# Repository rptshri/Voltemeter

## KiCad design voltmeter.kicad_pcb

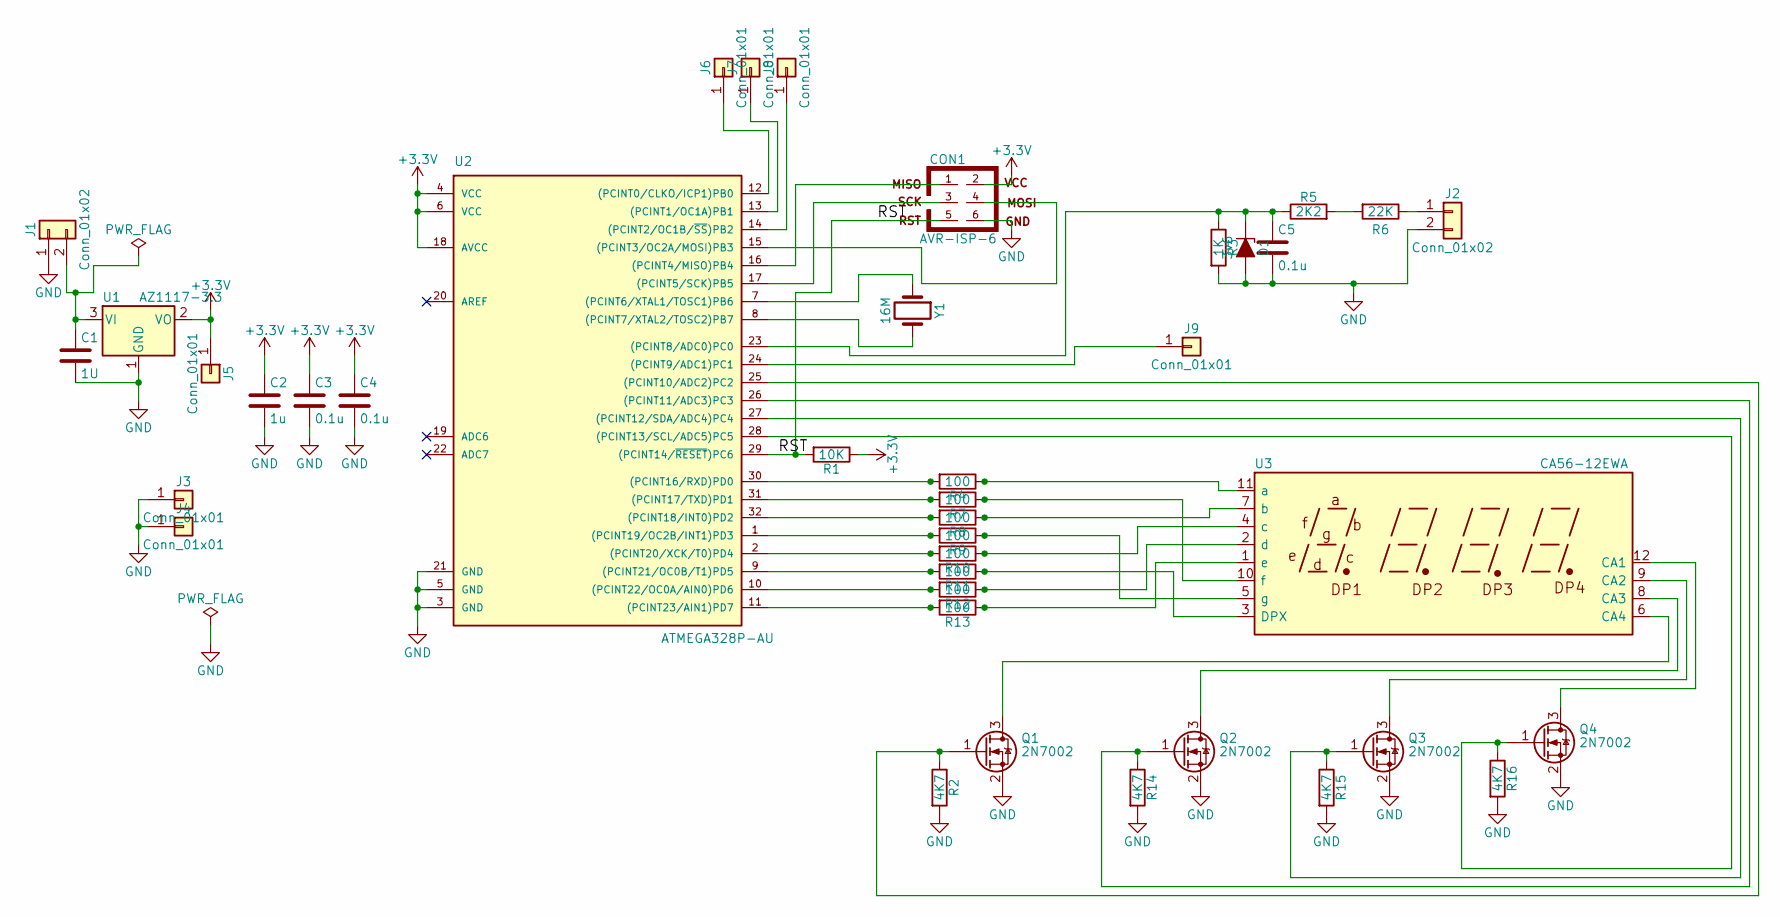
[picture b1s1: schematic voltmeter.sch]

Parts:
C1: 1U; C_0805_HandSoldering
C2: 1u; C_0805_HandSoldering
C3, C4, C5: 0.1u; C_0805_HandSoldering
CON1: AVR-ISP-6; Pin_Header_Straight_2x03_Pitch2.54mm
D1: 3v6; D_SMA
J1, J2: Conn_01x02; WAGO_734_2pin_Straight_RuggedPads
J3, J4, J5, J6, J7, J8, J9: Conn_01x01; Pin_Header_Straight_1x01_Pitch2.54mm
Q1, Q2, Q3, Q4: 2N7002; SOT-23
R1: 10K; R_0805_HandSoldering
R2, R14, R15, R16: 4K7; R_0805_HandSoldering
R3: 1K; R_0805_HandSoldering
R4, R7, R8, R9, R10, R11, R12, R13: 100; R_0805_HandSoldering
R5: 2K2; R_0805_HandSoldering
R6: 22K; R_0805_HandSoldering
U1: AZ1117-3.3; SOT-223-3_TabPin2
U2: ATMEGA328P-AU; TQFP-32_7x7mm_Pitch0.8mm
U3: CA56-12EWA
Y1: 16M; Crystal_HC18-U_Vertical

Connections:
+3V3: C2.1, C3.1, C4.1, CON1.2, J5.1, R1.1, U1.2 (VO), U2.4 (VCC), U2.6 (VCC), U2.18 (AVCC)
/RST: CON1.5, R1.2, U2.29 ((PCINT14/~RESET~)PC6)
GND: C1.2, C2.2, C3.2, C4.2, C5.2, CON1.6, D1.2 (A), J1.1, J2.2, J3.1, J4.1, Q1.2 (S), Q2.2 (S), Q3.2 (S), Q4.2 (S), R2.2, R3.2, R14.2, R15.2, R16.2, U1.1 (GND), U2.3 (GND), U2.5 (GND), U2.21 (GND)
unnamed: C1.1, J1.2, U1.3 (VI)
unnamed: C5.1, D1.1 (K), R3.1, R5.1, U2.23 ((PCINT8/ADC0)PC0)
unnamed: CON1.1, U2.16 ((PCINT4/MISO)PB4)
unnamed: CON1.3, U2.17 ((PCINT5/SCK)PB5)
unnamed: CON1.4, U2.15 ((PCINT3/OC2A/MOSI)PB3)
unnamed: J2.1, R6.1
unnamed: J6.1, U2.12 ((PCINT0/CLKO/ICP1)PB0)
unnamed: J7.1, U2.13 ((PCINT1/OC1A)PB1)
unnamed: J8.1, U2.14 ((PCINT2/OC1B/~SS~)PB2)
unnamed: J9.1, U2.24 ((PCINT9/ADC1)PC1)
unnamed: Q1.1 (G), R2.1, U2.25 ((PCINT10/ADC2)PC2)
unnamed: Q1.3 (D), U3.6 (CA4)
unnamed: Q2.1 (G), R14.1, U2.26 ((PCINT11/ADC3)PC3)
unnamed: Q2.3 (D), U3.8 (CA3)
unnamed: Q3.1 (G), R15.1, U2.27 ((PCINT12/SDA/ADC4)PC4)
unnamed: Q3.3 (D), U3.9 (CA2)
unnamed: Q4.1 (G), R16.1, U2.28 ((PCINT13/SCL/ADC5)PC5)
unnamed: Q4.3 (D), U3.12 (CA1)
unnamed: R4.1, U3.11 (a)
unnamed: R4.2, U2.30 ((PCINT16/RXD)PD0)
unnamed: R5.2, R6.2
unnamed: R7.1, U3.10 (f)
unnamed: R7.2, U2.31 ((PCINT17/TXD)PD1)
unnamed: R8.1, U3.7 (b)
unnamed: R8.2, U2.32 ((PCINT18/INT0)PD2)
unnamed: R9.1, U3.5 (g)
unnamed: R9.2, U2.1 ((PCINT19/OC2B/INT1)PD3)
unnamed: R10.1, U3.4 (c)
unnamed: R10.2, U2.2 ((PCINT20/XCK/T0)PD4)
unnamed: R11.1, U3.3 (DPX)
unnamed: R11.2, U2.9 ((PCINT21/OC0B/T1)PD5)
unnamed: R12.1, U3.2 (d)
unnamed: R12.2, U2.10 ((PCINT22/OC0A/AIN0)PD6)
unnamed: R13.1, U3.1 (e)
unnamed: R13.2, U2.11 ((PCINT23/AIN1)PD7)
unnamed: U2.7 ((PCINT6/XTAL1/TOSC1)PB6), Y1.1
unnamed: U2.8 ((PCINT7/XTAL2/TOSC2)PB7), Y1.2

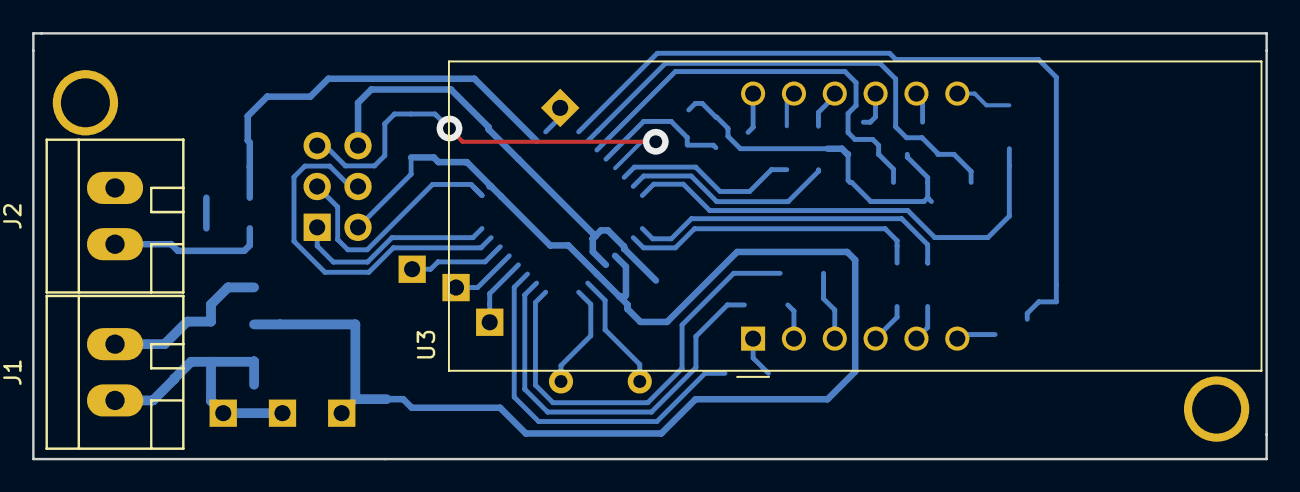
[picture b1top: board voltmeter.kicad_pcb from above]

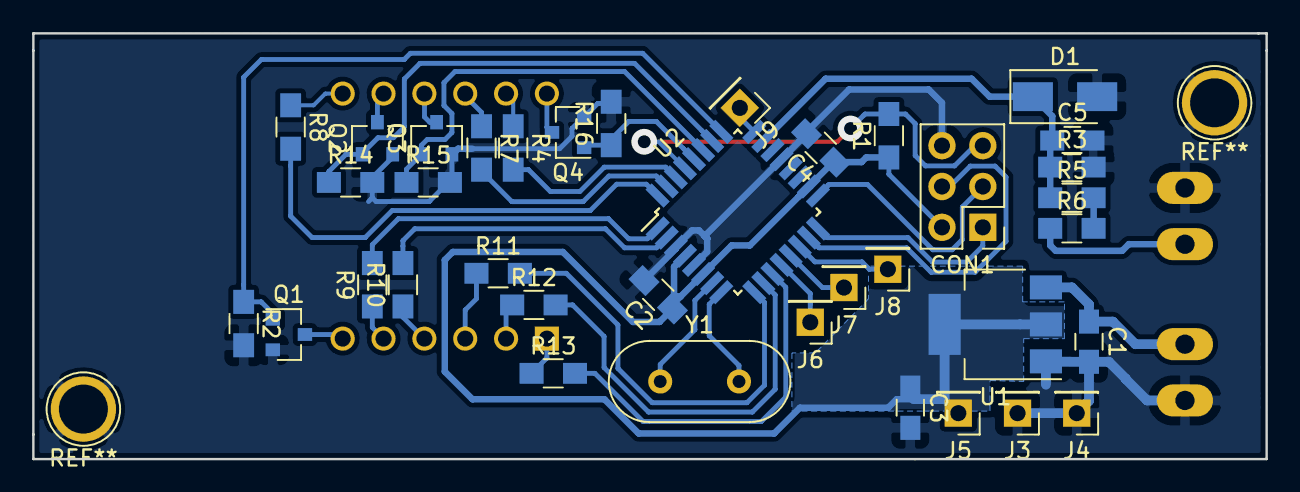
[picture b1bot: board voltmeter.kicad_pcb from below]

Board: 2 copper layers, 76.7 x 26.5 mm, 40 parts (37 on the bottom side), 40 nets.

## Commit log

2017-11-18 Commits just before KiCad crashed
2017-11-18 Closing commit
2017-12-02 Update PCB
2017-12-02 Modified tracks
2017-12-02 Added incomplete README
2020-05-25 [ImgBot] Optimize images
    /gerbers/voltmeter-B.Cu.svg -- 77.22kb -> 65.04kb (15.77%)
